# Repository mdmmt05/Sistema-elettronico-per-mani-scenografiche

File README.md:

# Nato Due Volte — Scenic Robotic Hands Control System

<div align="center">

</div>

> 🇮🇹 [Italiano](#italiano) · 🇬🇧 [English](#english)

---

# Italiano

## Descrizione

**Nato Due Volte** è un carro carnevalesco presentato alla **73ª edizione del Carnevale di Massafra**. Questa repository documenta il sistema elettronico e firmware realizzato per controllare due **mani scenografiche robotizzate**, ciascuna dotata di cinque dita mosse indipendentemente da servomotori.

Il sistema utilizza un **telecomando palmare personalizzato** che comunica via radio con due unità di controllo indipendenti, una per mano. Ogni unità è basata su Arduino Mega 2560 e su una shield progettata su misura; il telecomando è basato su Arduino Nano con una propria shield dedicata.

## Stato e validazione

Questo progetto è stato **progettato, costruito, programmato, integrato e collaudato fisicamente** per l'impiego sul carro.

A differenza di altri repository presenti nel profilo, la progettazione elettronica, il firmware e l'integrazione sono stati svolti **prevalentemente direttamente dall'autore**, con un approccio hands-on. Il sistema è stato inoltre testato in condizioni operative reali.

Il progetto rappresenta quindi uno dei lavori più direttamente indicativi delle competenze pratiche dell'autore in elettronica embedded, PCB, integrazione hardware-software e collaudo.

## Obiettivi progettuali

I requisiti principali erano:

- controllo indipendente di due mani;
- cinque servomotori per mano;
- comando wireless affidabile;
- interfaccia semplice per un operatore non tecnico;
- installazione e manutenzione semplici durante l'allestimento del carro;
- alimentazione separata e adeguata al carico dei servomotori;
- possibilità di selezionare più sequenze/movimenti per ciascuna mano.

## Architettura

```mermaid
flowchart LR
    OP[Operatore] --> REMOTE[Telecomando
Arduino Nano]
    REMOTE -->|nRF24L01+| CTRL1[Controller mano 1
Arduino Mega]
    REMOTE -->|nRF24L01+| CTRL2[Controller mano 2
Arduino Mega]
    CTRL1 --> S1[5 servomotori]
    CTRL2 --> S2[5 servomotori]
```

Il telecomando consente di inviare fino a **7 comandi di movimento** a ciascuna mano mediante combinazioni di pulsanti.

## Hardware

| Componente | Quantità | Funzione |
|---|---:|---|
| Arduino Mega 2560 | 2 | Unità di controllo delle mani |
| Arduino Nano | 1 | Telecomando |
| nRF24L01+ | 3 | Comunicazione radio |
| Shield personalizzata Mega | 2 | RF, connettori e distribuzione segnali |
| Shield personalizzata Nano | 1 | Pulsanti e modulo RF |
| Servomotori | 10 | Attuazione delle dita |
| Alimentatore 5 V / min. 8 A | 2 | Alimentazione delle mani |
| Powerbank 5 V | 1 | Alimentazione telecomando |

### Collegamento servomotori

| Connettore | Indice firmware | Dito |
|---|---:|---|
| J3 | 0 | Pollice |
| J4 | 1 | Indice |
| J5 | 2 | Medio |
| J6 | 3 | Anulare |
| J7 | 4 | Mignolo |

## Repository

```text
nato-due-volte/
├── controller_code.ino
├── code_telecomando.ino
└── manuale_di_installazione.docx
```

## Installazione firmware

Prerequisiti:

- Arduino IDE;
- libreria RF24.

Per ogni Arduino Mega, impostare `USE_FIRST` in modo coerente con il controller da programmare, quindi caricare `controller_code.ino`. Caricare `code_telecomando.ino` sull'Arduino Nano.

> Caricare entrambe le unità con la stessa configurazione può far rispondere entrambe le mani allo stesso comando.

Per cablaggio, alimentazione e troubleshooting fare riferimento al manuale di installazione.

## Demo

I video `natoduevolte.mp4` e `mano.mp4` mostrano il sistema fisico in funzione.

---

# English

## Project description

**Nato Due Volte** (*Born Twice*) was a carnival float presented at the **73rd edition of the Carnevale di Massafra**. This repository documents the electronics and firmware built to control two **scenic robotic hands**, each with five independently actuated servo-driven fingers.

A custom handheld remote communicates by RF with two independent control units, one for each hand. Each hand controller uses an Arduino Mega 2560 and a custom shield, while the remote uses an Arduino Nano with its own custom shield.

## Status and validation

This project was **designed, built, programmed, integrated, and physically tested** for use on the float.

Unlike some other repositories in this profile, the electronics design, firmware implementation, and system integration were performed **primarily directly by the author** through a hands-on development process. The finished system was tested in real operating conditions.

For that reason, this repository is one of the most representative examples of the author's practical work in embedded electronics, PCB design, hardware-software integration, and field testing.

## Design requirements

The main requirements were:

- independent control of two hands;
- five servos per hand;
- reliable wireless operation;
- simple interaction for a non-technical operator;
- straightforward installation and maintenance;
- adequate power delivery for the servo load;
- multiple selectable motion commands for each hand.

## Architecture

```mermaid
flowchart LR
    OP[Operator] --> REMOTE[Handheld remote
Arduino Nano]
    REMOTE -->|nRF24L01+| CTRL1[Hand controller 1
Arduino Mega]
    REMOTE -->|nRF24L01+| CTRL2[Hand controller 2
Arduino Mega]
    CTRL1 --> S1[5 servos]
    CTRL2 --> S2[5 servos]
```

The remote can send up to **7 motion commands** to each hand through button combinations.

## Hardware

| Component | Qty | Purpose |
|---|---:|---|
| Arduino Mega 2560 | 2 | Hand control units |
| Arduino Nano | 1 | Handheld remote |
| nRF24L01+ | 3 | RF communication |
| Custom Mega shield | 2 | RF and servo interfacing |
| Custom Nano shield | 1 | Buttons and RF interface |
| Servo motors | 10 | Finger actuation |
| 5 V / min. 8 A PSU | 2 | Hand power supply |
| 5 V power bank | 1 | Remote power supply |

## Repository structure

```text
nato-due-volte/
├── controller_code.ino
├── code_telecomando.ino
└── manuale_di_installazione.docx
```

## Firmware installation

Requirements:

- Arduino IDE;
- RF24 library.

Configure `USE_FIRST` appropriately for each Mega controller before uploading `controller_code.ino`. Upload `code_telecomando.ino` to the Arduino Nano.

For wiring, power-supply details, and troubleshooting, see the installation manual.

## Demo

The files `natoduevolte.mp4` and `mano.mp4` show the physical system in operation.

## License

MIT License. See `LICENSE`.

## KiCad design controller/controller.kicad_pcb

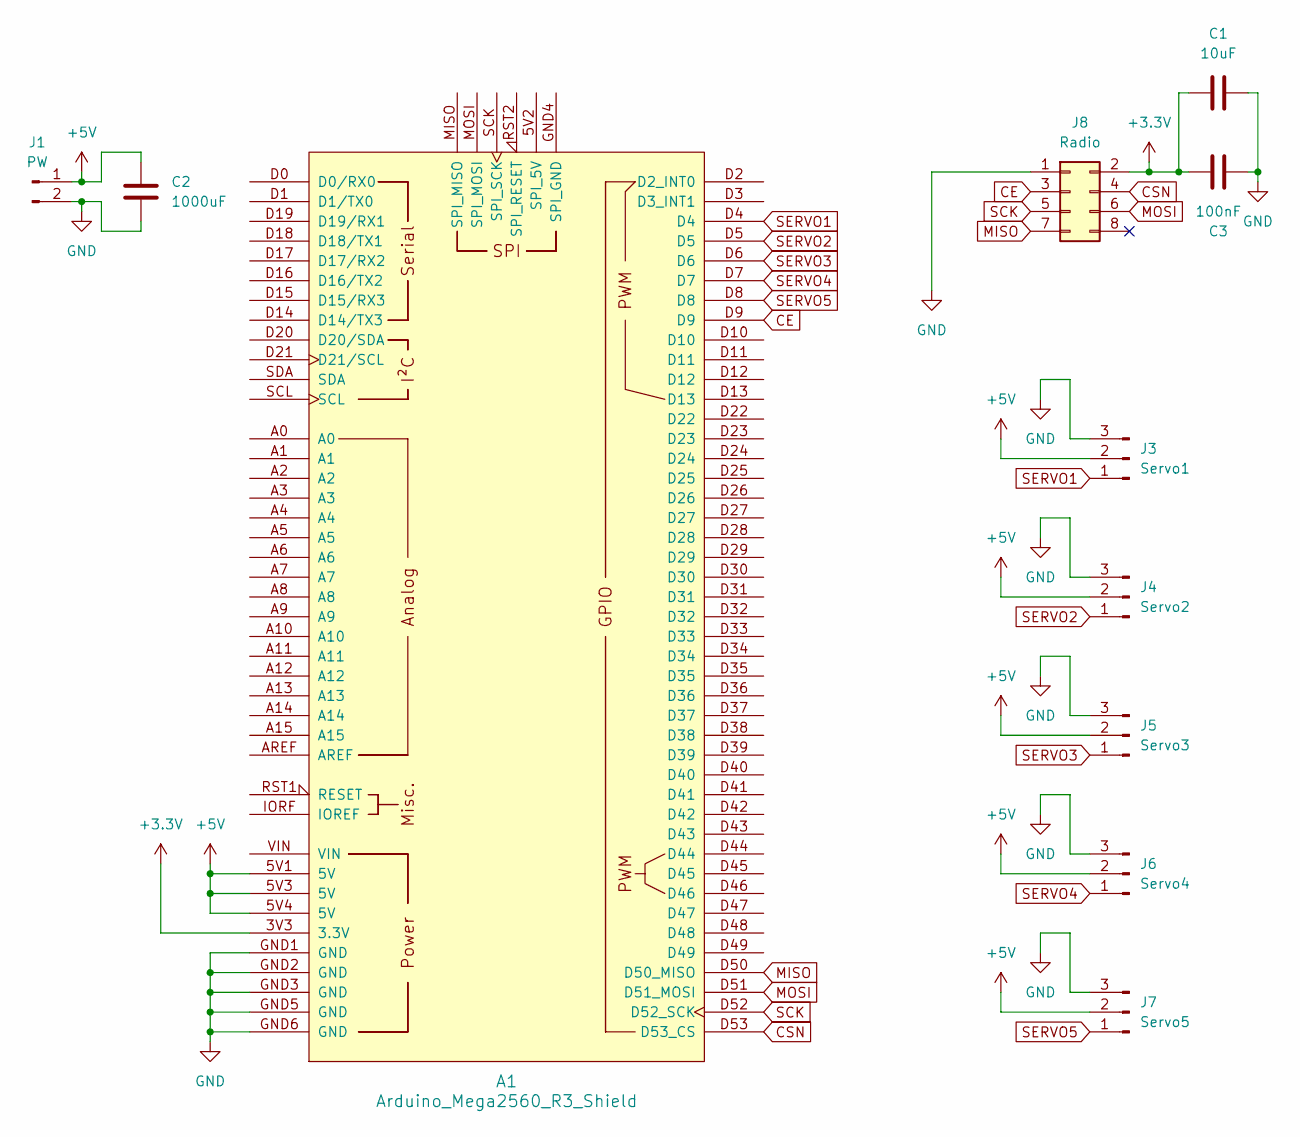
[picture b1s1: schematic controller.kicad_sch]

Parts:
A1: Arduino_Mega2560_R3_Shield
C1: 10uF; C_0402_1005Metric_Pad0.74x0.62mm_HandSolder
C2: 1000uF; CP_Elec_8x10.5
C3: 100nF; C_0402_1005Metric_Pad0.74x0.62mm_HandSolder
J1: PW; PinHeader_1x02_P2.54mm_Vertical
J3: Servo1; PinHeader_1x03_P2.54mm_Vertical
J4: Servo2; PinHeader_1x03_P2.54mm_Vertical
J5: Servo3; PinHeader_1x03_P2.54mm_Vertical
J6: Servo4; PinHeader_1x03_P2.54mm_Vertical
J7: Servo5; PinHeader_1x03_P2.54mm_Vertical
J8: Radio; PinHeader_2x04_P2.54mm_Vertical

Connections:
+3.3V: A1.3V3 (3.3V), C1.1, C3.2, J8.2
+5V: A1.5V1 (5V), A1.5V3 (5V), A1.5V4 (5V), C2.2, J1.1, J3.2, J4.2, J5.2, J6.2, J7.2
CE: A1.D9, J8.3
CSN: A1.D53 (D53_CS), J8.4
GND: A1.GND1 (GND), A1.GND2 (GND), A1.GND3 (GND), A1.GND5 (GND), A1.GND6 (GND), C1.2, C2.1, C3.1, J1.2, J3.3, J4.3, J5.3, J6.3, J7.3, J8.1
MISO: A1.D50 (D50_MISO), J8.7
MOSI: A1.D51 (D51_MOSI), J8.6
SCK: A1.D52 (D52_SCK), J8.5
SERVO1: A1.D4, J3.1
SERVO2: A1.D5, J4.1
SERVO3: A1.D6, J5.1
SERVO4: A1.D7, J6.1
SERVO5: A1.D8, J7.1

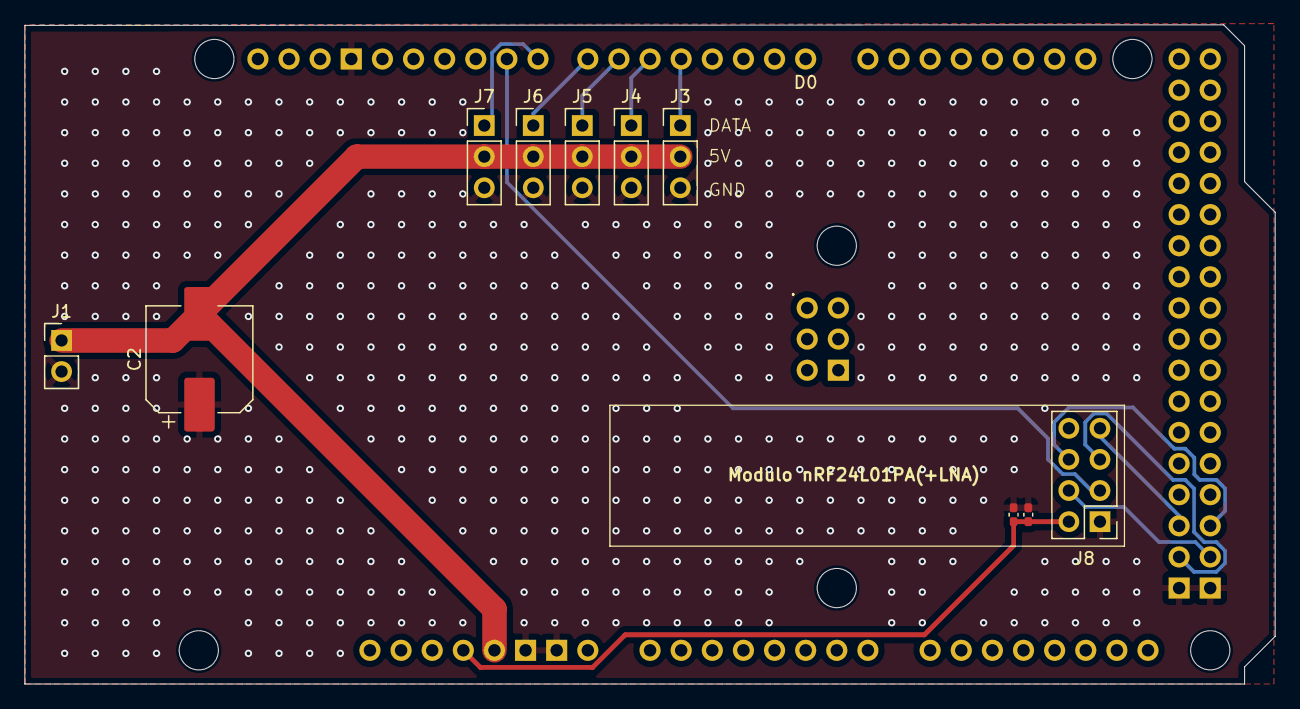
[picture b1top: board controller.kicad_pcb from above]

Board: 2 copper layers, 102.1 x 53.8 mm, 11 parts (0 on the bottom side), 13 nets.

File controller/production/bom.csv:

Designator,Footprint,Quantity,Value,LCSC Part #
A1,Arduino_Mega2560_R3_Shield,1,Arduino_Mega2560_R3_Shield,
C1,0402,1,10uF,
C2,CP_Elec_8x10.5,1,1000uF,
C3,0402,1,100nF,
J1,PinHeader_1x02_P2.54mm_Vertical,1,PW,
J3,PinHeader_1x03_P2.54mm_Vertical,1,Servo1,
J4,PinHeader_1x03_P2.54mm_Vertical,1,Servo2,
J5,PinHeader_1x03_P2.54mm_Vertical,1,Servo3,
J6,PinHeader_1x03_P2.54mm_Vertical,1,Servo4,
J7,PinHeader_1x03_P2.54mm_Vertical,1,Servo5,
J8,PinHeader_2x04_P2.54mm_Vertical,1,Radio,

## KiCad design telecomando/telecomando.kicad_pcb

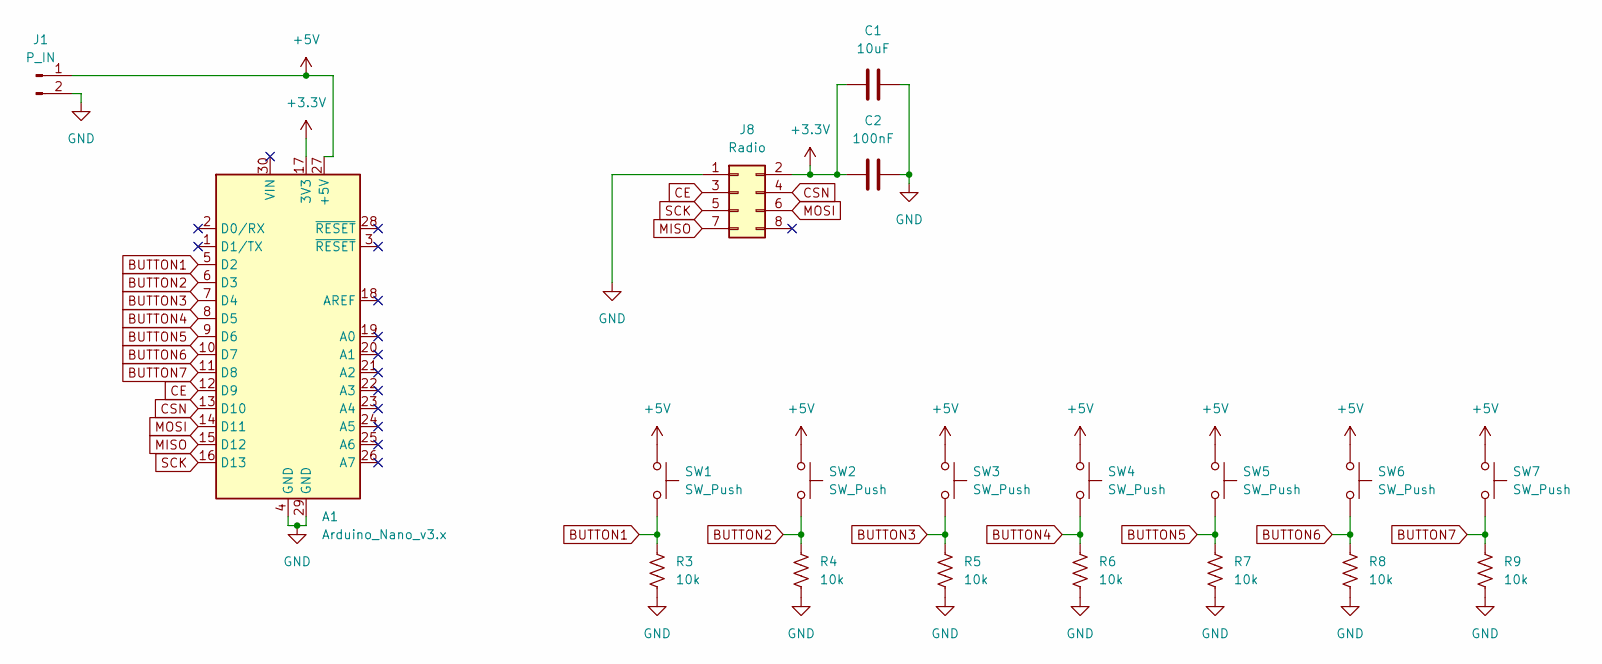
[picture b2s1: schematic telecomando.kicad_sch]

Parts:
A1: Arduino_Nano_v3.x; Arduino_Nano
C1: 10uF; C_0402_1005Metric_Pad0.74x0.62mm_HandSolder
C2: 100nF; C_0402_1005Metric_Pad0.74x0.62mm_HandSolder
J1: P_IN; PinHeader_1x02_P2.54mm_Vertical
J8: Radio; PinHeader_2x04_P2.54mm_Vertical
R3, R4, R5, R6, R7, R8, R9: 10k; R_0402_1005Metric_Pad0.72x0.64mm_HandSolder
SW1, SW2, SW3, SW4, SW5, SW6, SW7: SW_Push; SW_Cherry_MX_1.00u_PCB

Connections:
+3.3V: A1.17 (3V3), C1.1, C2.1, J8.2
+5V: A1.27 (+5V), J1.1, SW1.1, SW2.1, SW3.1, SW4.1, SW5.1, SW6.1, SW7.1
BUTTON1: A1.5 (D2), R3.1, SW1.2
BUTTON2: A1.6 (D3), R4.1, SW2.2
BUTTON3: A1.7 (D4), R5.1, SW3.2
BUTTON4: A1.8 (D5), R6.1, SW4.2
BUTTON5: A1.9 (D6), R7.1, SW5.2
BUTTON6: A1.10 (D7), R8.1, SW6.2
BUTTON7: A1.11 (D8), R9.1, SW7.2
CE: A1.12 (D9), J8.3
CSN: A1.13 (D10), J8.4
GND: A1.4 (GND), A1.29 (GND), C1.2, C2.2, J1.2, J8.1, R3.2, R4.2, R5.2, R6.2, R7.2, R8.2, R9.2
MISO: A1.15 (D12), J8.7
MOSI: A1.14 (D11), J8.6
SCK: A1.16 (D13), J8.5

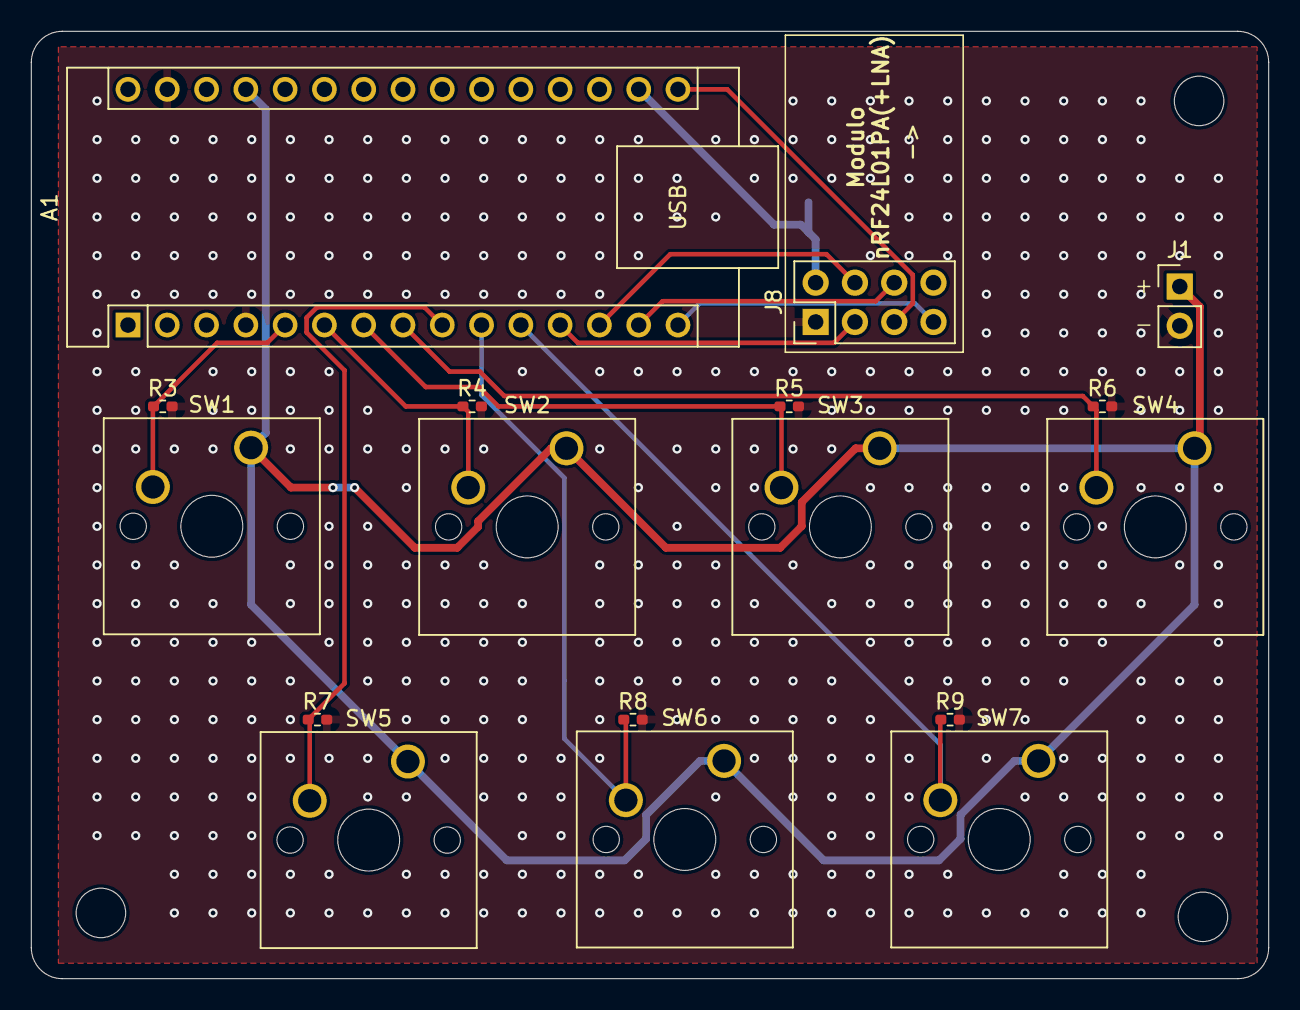
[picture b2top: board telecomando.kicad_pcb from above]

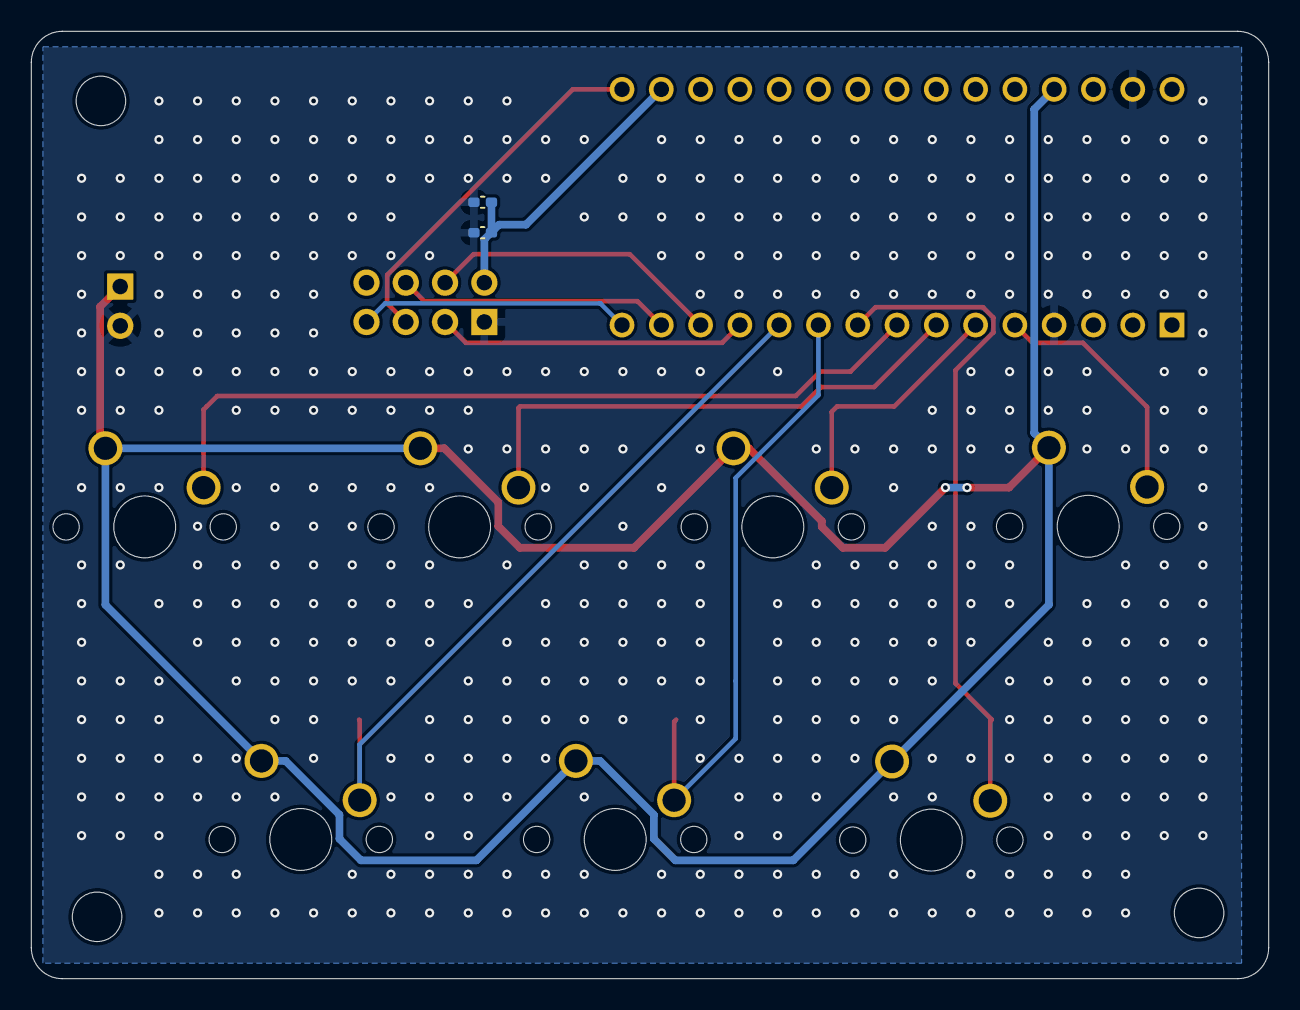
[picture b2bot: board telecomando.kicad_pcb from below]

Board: 2 copper layers, 80.0 x 61.2 mm, 19 parts (2 on the bottom side), 15 nets.

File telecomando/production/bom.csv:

Designator,Footprint,Quantity,Value,LCSC Part #
A1,Arduino_Nano,1,Arduino_Nano_v3.x,
C1,0402,1,10uF,
C2,0402,1,100nF,
J1,PinHeader_1x02_P2.54mm_Vertical,1,P_IN,
J8,PinHeader_2x04_P2.54mm_Vertical,1,Radio,
"R3, R4, R5, R6, R7, R8, R9",0402,7,10k,
"SW1, SW2, SW3, SW4, SW5, SW6, SW7",SW_Cherry_MX_1.00u_PCB,7,SW_Push,

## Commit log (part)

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2026-02-22 First upload
2026-02-22 Replace placeholder images with video links
    Updated images and removed system overview section.
2026-02-22 Revise demo section in README for clarity
    Updated demo section to include video instructions and placeholders for images.
2026-06-08 Add photos section to README
    Added photos section with image to both Italian and English README.
2026-06-08 Update README with photo section and bilingual headings
    Reorganize photo section and add bilingual headings.
